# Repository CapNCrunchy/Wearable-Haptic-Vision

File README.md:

# Wearable-Haptic-Vision
Capstone project for UF CpE

# Project Architecture
"Wearable Haptic Vision" is a device that uses a wearable tactile display to inform the wearer about their surroundings by receiving object distance information. It will capture LiDAR depth information and utilize a Raspberry controller unit to make the wearable pressure waistband react according to an object's distance and direction.

## Pressure Waistband
The waistband will have embedded inflatable nodes that each have tubing connecting to a main housing unit that will hold the intake/exhaust controls (logic circuitry, pressure sensors, raspberry pi). There are 8 nodes that go across the waist and each will inflate according to the corresponding lidar information. For example, if an object is very close to the right side of the Lidar then the nodes on the right side will inflate to the max to represent the closest object. The inverse is also true that an object that is far away will be represented by a very deflated node.

## LiDAR Application
It is an iOS swift application taht utilizes the iphone built in LiDAR to retrieve location and distance information. It takes it as a full image map and then averages the values within the corresponding divisions. This is sent to the Raspberry Pi controller via BLE.

## Controller
The Raspberry Pi takes the lidar data and simplifies it into four states by distance. It then sends this data to the pressure regulator logic which switches between intake and exhaust to get to the correct state. This gives each node four distance/pressure states. 

# Completed Work 
- BLE reciever and Swift application connection
- Infalte/deflate valves for nodes
- Inflate/deflate Schematics w/ Rasperbery pi & modules
- Swift IOS application to interface with LIDAR
- Schematics and models for the vest & soft 3d-printed nodes

# Known Bugs/WIP
The newest physical model of inflatables and circuitry is still waiting to be printed.

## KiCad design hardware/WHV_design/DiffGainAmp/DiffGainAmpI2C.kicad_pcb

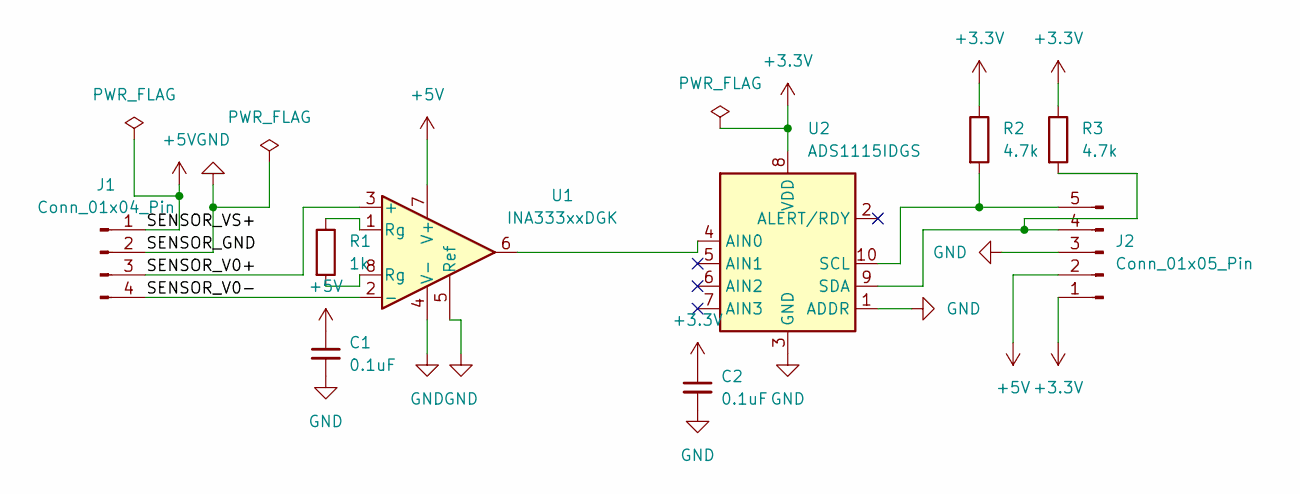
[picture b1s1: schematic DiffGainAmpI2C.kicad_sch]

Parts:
C1, C2: 0.1uF; C_0805_2012Metric
J1: Conn_01x04_Pin; PinHeader_1x04_P2.54mm_Vertical
J2: Conn_01x05_Pin; PinHeader_1x05_P2.54mm_Vertical
R1: 1k; R_0805_2012Metric
R2, R3: 4.7k; R_0805_2012Metric
U1: INA333xxDGK; VSSOP-8_3x3mm_P0.65mm
U2: ADS1115IDGS; VSSOP-10_3x3mm_P0.5mm

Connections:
+3.3V: C2.1, J2.1, R2.1, R3.1, U2.8 (VDD)
+5V: C1.1, J1.1, J2.2, U1.7 (V+)
/SENSOR_V0+: J1.3, U1.3 (+)
/SENSOR_V0-: J1.4, U1.2 (-)
GND: C1.2, C2.2, J1.2, J2.3, U1.4 (V-), U1.5 (Ref), U2.1 (ADDR), U2.3 (GND)
unnamed: J2.4, R3.2, U2.9 (SDA)
unnamed: J2.5, R2.2, U2.10 (SCL)
unnamed: R1.1, U1.1 (Rg)
unnamed: R1.2, U1.8 (Rg)
unnamed: U1.6, U2.4 (AIN0)

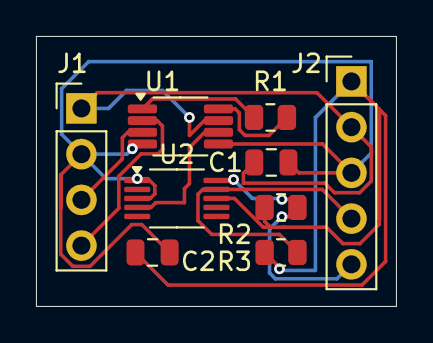
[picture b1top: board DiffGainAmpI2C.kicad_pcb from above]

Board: 2 copper layers, 20.0 x 15.0 mm, 9 parts (0 on the bottom side), 10 nets.

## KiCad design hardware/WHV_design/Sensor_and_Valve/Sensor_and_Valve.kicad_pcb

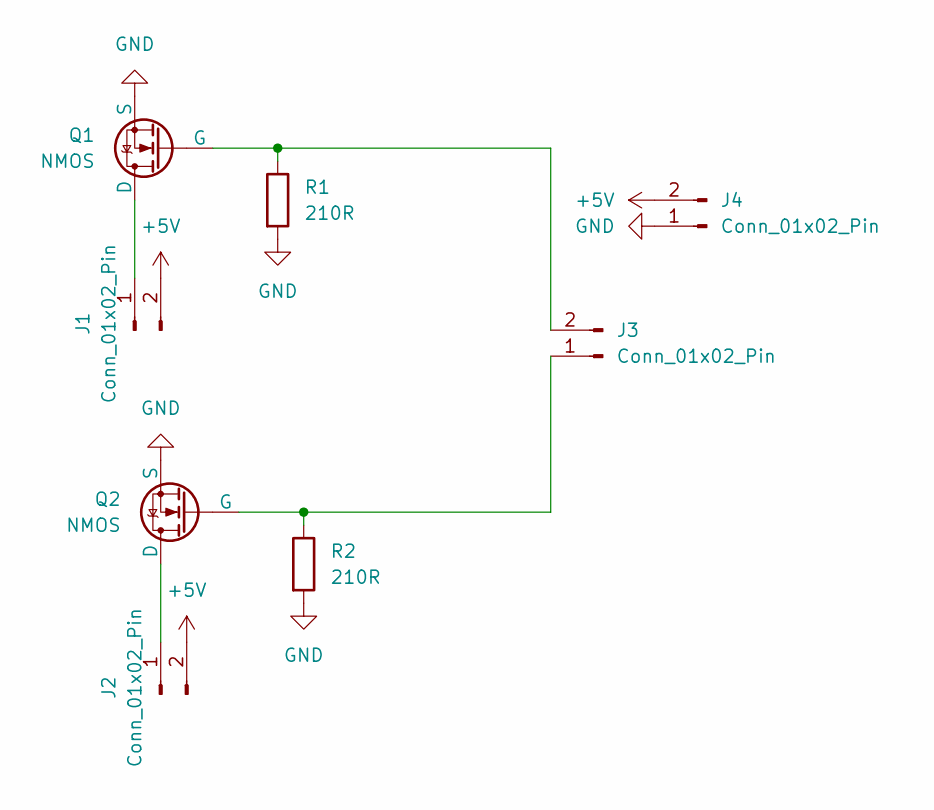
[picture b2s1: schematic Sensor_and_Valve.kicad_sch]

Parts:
J1, J2, J3, J4: Conn_01x02_Pin; JST_XH_B2B-XH-A_1x02_P2.50mm_Vertical
Q1, Q2: NMOS; SOT23_TOS
R1, R2: 210R; RESC1005X40N

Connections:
+5V: J1.2, J2.2, J4.2
GND: J4.1, Q1.3 (S), Q2.3 (S), R1.2, R2.2
unnamed: J1.1, Q1.1 (D)
unnamed: J2.1, Q2.1 (D)
unnamed: J3.1, Q2.2 (G), R2.1
unnamed: J3.2, Q1.2 (G), R1.1

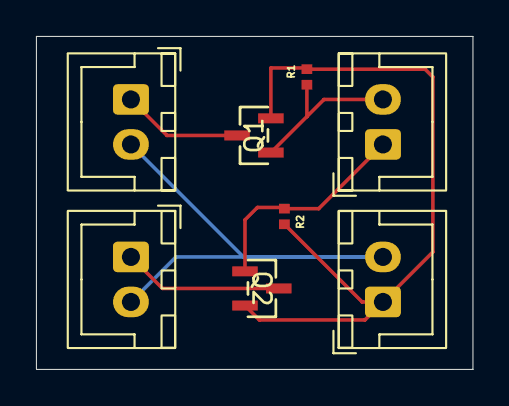
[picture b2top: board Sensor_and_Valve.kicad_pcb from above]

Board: 2 copper layers, 24.2 x 18.5 mm, 8 parts (0 on the bottom side), 6 nets.

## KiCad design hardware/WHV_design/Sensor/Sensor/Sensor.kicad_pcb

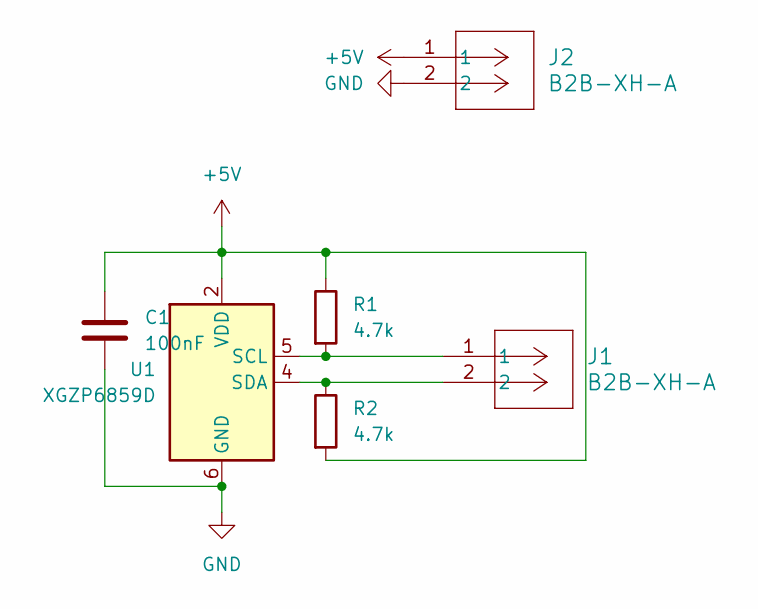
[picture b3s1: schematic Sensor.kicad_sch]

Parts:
C1: 100nF; WCAP-ATUL_6.3X11_DXL_
J1, J2: B2B-XH-A; CONN_B2B-XH-A_JST
R1, R2: 4.7k; RESC1005X40N
U1: XGZP6859D; CFSensor_XGZP6859D_7x7mm

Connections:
+5V: C1.1, J2.1, R1.1, R2.2, U1.2 (VDD)
GND: C1.2, J2.2, U1.6 (GND)
unnamed: J1.1, R1.2, U1.5 (SCL)
unnamed: J1.2, R2.1, U1.4 (SDA)

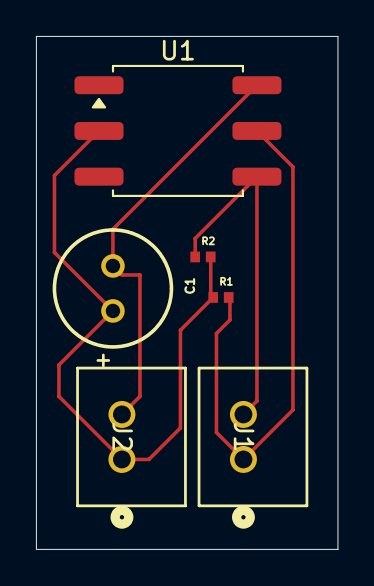
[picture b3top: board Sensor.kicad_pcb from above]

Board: 2 copper layers, 16.8 x 28.5 mm, 6 parts (0 on the bottom side), 4 nets.

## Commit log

2025-10-19 add gitignore for swift and xcode
2025-10-19 (lidar) init swift project
2025-10-20 (lidar) rough implementation of BluetoothManager + device scanning, untested
2025-10-20 (lidar) specify NSBluetoothAlwaysUsageDescription
2025-10-20 (lidar) scan based on state change
2025-10-20 (lidar) change min RSSI to be -60 so it can discover the pi
2025-10-23 add rust to gitignore
2025-10-23 (ble) basic example for ble peripheral
2025-10-23 (ble) use system_includes for name
2025-10-23 (ble) actually specify the features
2025-10-23 (ble) only include localname
2025-10-23 (ble) remove it actually
2025-10-26 (lidar) finish bluetooth connectivity sending mock data
2025-10-26 (lidar) actually stage the files before commit
2025-10-26 simple ble central with characteristic writing for prototyping
2025-10-26 write random data every 5 seconds
2025-10-26 Create server.pi and first test for BLE server communications with iPhone
2025-10-26 Corrected file type
2025-10-26 Update main.rs to get GATT up and running for BLE
2025-10-26 first draft of soft nodes w/ part and part drawing
2025-10-26 Update main.rs to use correct bluer version
2025-10-26 Update Cargo.toml to use correct bluer version
2025-10-26 Update Cargo.toml upgrade to ver 17 of bluer
2025-10-26 Update main.rs upgrade bluer to ver 17
2025-10-27 schematic for vest
    mocked up on google slides, will work on 3d model but wanted to have a nice 2d layout fist
2025-10-27 vest schematic 1
    mocked up on google slides, will work on 3d model with pneumatic simulation. wanted to get an 2d schematic to potentially also start creating real mockups
2025-10-27 Update Cargo.toml Added bluetoothd feature
2025-10-27 Update main.rs Working BLE with iPhone!
2025-10-27 hardware schematics and datasheets
2025-10-27 updated ReadMe with architecture and completed work
    Added project architecture and completed work sections.
2025-10-27 Add known bugs section to README
2025-11-14 Update main.rs to accept JSON as 2D array and parses it then save it into a grid ands save a recent history
2025-11-14 (lidar) connections work, update state in UI
2025-11-14 (lidar) use specific writing characteristic, discover peripheral characteristics
2025-11-14 depth map capture + view
2025-11-14 (lidar) camera permissions
2025-11-14 (lidar) use depth map view instead of BLE transmitter
2025-11-14 Bare bones microcontroller code
2025-11-15 Updated node controller with state mapping (1-4) and automatic actuation logic
2025-11-15 added individual pin values for each states
2025-11-15 added serialport dependency
2025-11-15 wired gridmap to 4 states for uart node controller
2025-11-15 Rollback changes to main.rs due to build failures
2025-11-15 testing pi to microcontroller implementation
2025-11-15 updated logic for processing gridmap and sending to feather
2025-11-15 fixed process payload function
2025-11-15 added print statement to view raw bytes from array
2025-11-16 fixed async func
2025-11-16 Update main.rs to use if00
2025-11-17 Pneumatic Assembly System V1
2025-11-17 molds/ stencils for flat pneumatic nodes
2026-01-30 exploration and redesign of hardware
2026-01-30 added schematic for node regulator
2026-01-30 (lidar) begin on a new app view (claude-generated prototype)
2026-01-30 (lidar) data send toggling
2026-01-30 (lidar) split into mock and BLE devices / managers, apply to app view
2026-01-30 (lidar) add unique identifiers to mock devices
2026-01-30 (lidar) try building and deploying to testflight
2026-01-30 (lidar) allow workflow dispatches
2026-01-30 (lidar) specify ruby version
2026-01-30 (lidar) fix bad path
2026-01-30 (lidar) fix up paths
2026-01-30 (lidar) specify platform
2026-01-30 reorganized and newest model with tpu layers/ silicone layer.
2026-01-30 Full flat pneumatic design with new value design
    Help to visualize and with new schematic conner made
2026-01-31 backlog update
2026-02-11 Mega changes on the schematics and pcb
2026-02-19 disable ios workflow
2026-02-19 session view
2026-02-19 start building collection service
2026-02-20 silicone and tpu nodes
2026-02-22 Uploaded potential speed fix based
    These are untested changes on our original main.rs that uses our projects old architecture so it is really just here for record keeping
2026-02-22 Uploaded shell/template code for new architecture
2026-02-22 Update main_shell.rs
    Changing main_shell.rs to reflect our groups changes to the esp32 for ble rather than the use of the pi
2026-02-23 migrated esp32 receiver from rust to c++
2026-02-23 updated to store current state and handle raw bytes instead of json
2026-02-23 start/stop button (coupled with session logic)
2026-02-23 lidar display view
2026-02-23 CollectionService should also conform to ObservableObject
2026-02-23 queue data sent instead of sending all at once
2026-02-23 app view + switch content view to use app view
2026-02-23 fix device scanning by using observed device manager
2026-02-23 DeviceManagers should always conform to ObservableObject
2026-02-23 publish in mock too
2026-02-23 publish BLE state for UI
2026-02-23 throttle lidar to 30 hz
2026-02-23 mock collection service
2026-02-25 Add files via upload
    added esp32 pressure and mux func for 4 nodes
2026-02-26 Pin outputs all driven high for demo
2026-02-26 external ui remote in progress
    Need to add indents for braile and designs for buttons itself
2026-03-11 Fixed footprints and redid valve pcb
2026-03-23 Added DiffGainAmp KiCad w/ gerber and drill files
2026-03-23 Added zip for easy download and access
2026-04-08 redid nodes
    thinner and with 8 nodes
2026-04-15 Add 8 node control loop
2026-04-22 zip file with new 8-node instances
    need to make thicker for future development
2026-04-22 external remote mockup
2026-04-22 publish BLE connection for live UI updates
2026-04-22 persist BLE connections
2026-04-22 conform to protocol
2026-04-22 use session manager for BLE LiDAR sessions
2026-04-22 observe changes in device connection, manage sessions thru SessionManager
2026-04-22 add landscape support
2026-04-22 add action intent for sessions
2026-04-22 method to announce LiDAR reconnects
